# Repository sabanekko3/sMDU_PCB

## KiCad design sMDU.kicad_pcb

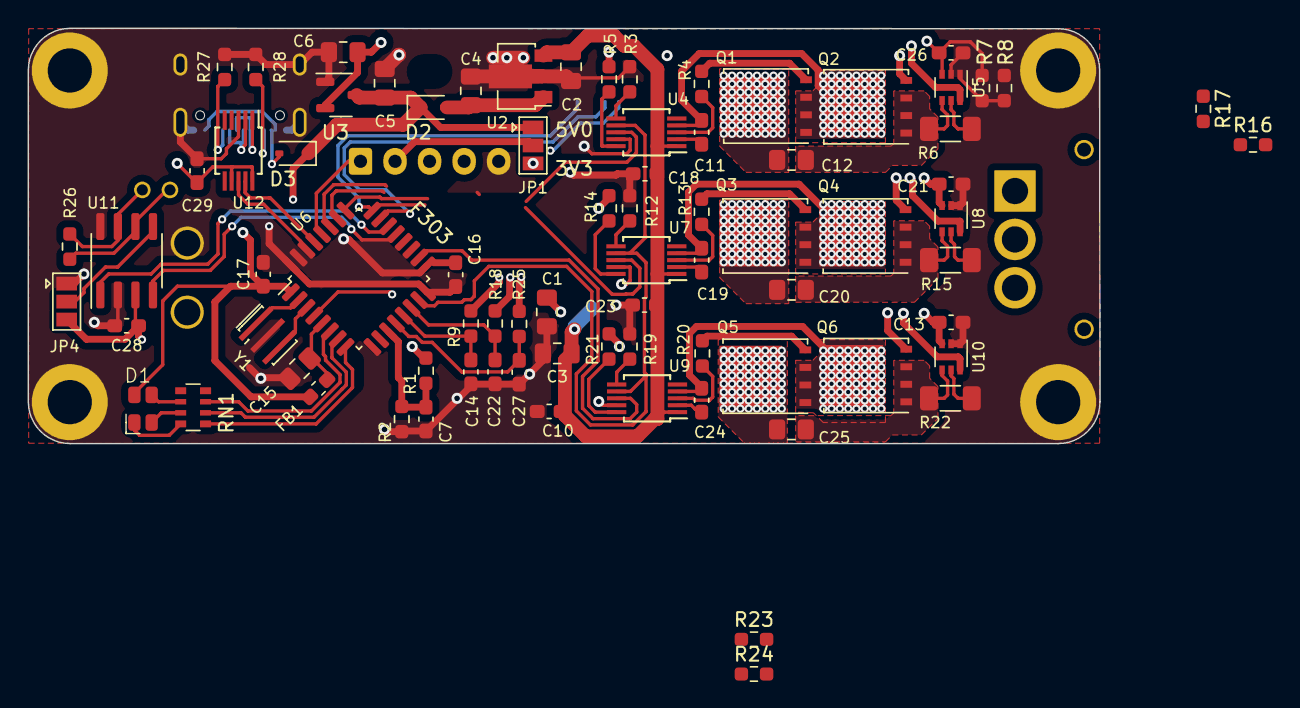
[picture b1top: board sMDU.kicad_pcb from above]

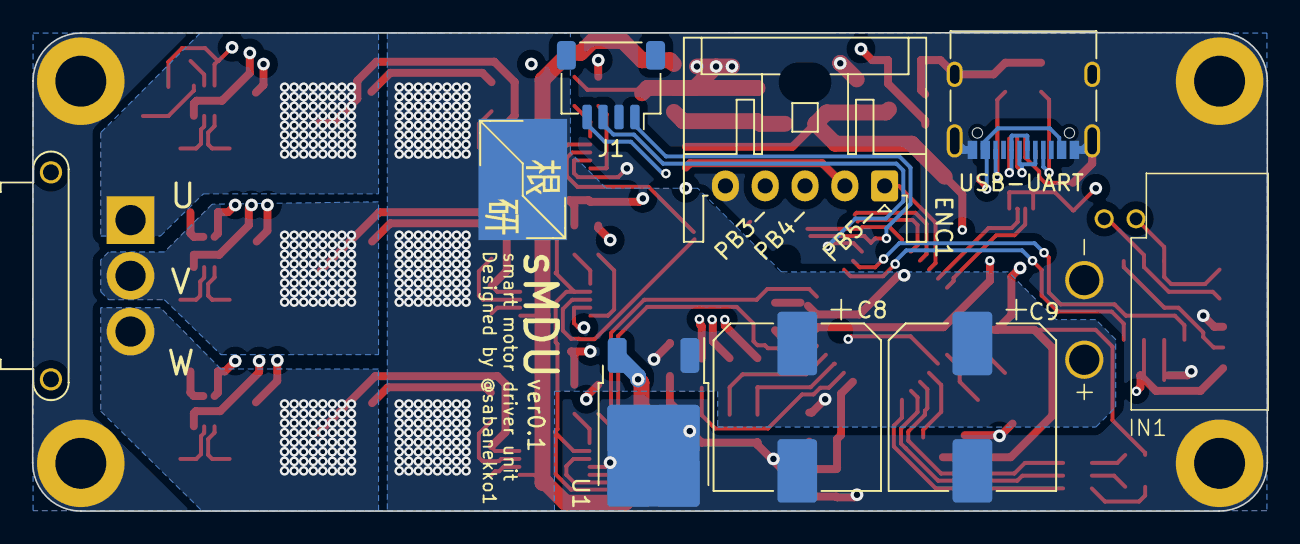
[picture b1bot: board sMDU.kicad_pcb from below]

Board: 4 copper layers, 77.6 x 30.1 mm, 91 parts (9 on the bottom side), 71 nets.

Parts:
C1, C2, C3, C4, C5, C6, C12, C15, C20, C25: 4.7u; C_0805_2012Metric_Pad1.18x1.45mm_HandSolder
C7, C13, C16, C17, C21, C26, C28, C29: 0.1u; C_0603_1608Metric_Pad1.08x0.95mm_HandSolder
C8, C9: 330u; CP_Elec_10x10
C10, C11, C18, C19, C23, C24: 1u; C_0603_1608Metric_Pad1.08x0.95mm_HandSolder
C14, C22, C27: 0.01u; C_0603_1608Metric_Pad1.08x0.95mm_HandSolder
D1: LED_BARG; SMD,1.8x2mm
D2, D3: D; D_SOD-323
ENC1: Conn_01x05; JST_XA_S05B-XASK-1_1x05_P2.50mm_Horizontal
FB1: FerriteBead; L_0603_1608Metric_Pad1.05x0.95mm_HandSolder
H1, H2, H3, H4: MountingHole_Pad; MountingHole_3.2mm_M3_ISO14580_Pad
IN1: XT30PW22
J1: Conn_01x04; JST_SH_SM04B-SRSS-TB_1x04-1MP_P1.00mm_Horizontal
J2: USB_C_Receptacle_USB2.0; USB_C_Receptacle_XKB_U262-16XN-4BVC11
JP1: C2P; SolderJumper-3_P1.3mm_Open_Pad1.0x1.5mm
JP4: Jumper_3_Open; SolderJumper-3_P1.3mm_Open_Pad1.0x1.5mm
OUT1: Conn_01x03; AMASS_MR30PW-FB_1x03_P3.50mm_Horizontal
Q1, Q2, Q3, Q4, Q5, Q6: SWHA088R06VT; TDSON-8-1
R1, R7, R8, R16, R17, R23, R24: 10k; R_0603_1608Metric_Pad0.98x0.95mm_HandSolder
R2: 1k; R_0603_1608Metric_Pad0.98x0.95mm_HandSolder
R3, R12, R19: 100k; R_0603_1608Metric_Pad0.98x0.95mm_HandSolder
R4, R5, R13, R14, R20, R21: 22; R_0603_1608Metric_Pad0.98x0.95mm_HandSolder
R6, R15, R22: 1m; R_1206_3216Metric_Pad1.30x1.75mm_HandSolder
R9, R18, R25: 100; R_0603_1608Metric_Pad0.98x0.95mm_HandSolder
R26: 120; R_0603_1608Metric_Pad0.98x0.95mm_HandSolder
R27, R28: 5.1k; R_0603_1608Metric_Pad0.98x0.95mm_HandSolder
RN1: 1k; R_Array_Convex_4x0603
TP1: LOGO; sabanegi
U1: 9V_LR; TO-252-2
U2: L78L05_SOT89; SOT-89-3
U3: XC6206PxxxMR; SOT-23-3
U4, U7, U9: DGD0506A; MSOP-10_3x3mm_P0.5mm
U5, U8, U10: INA199x1DCK; SOT-363_SC-70-6
U6: STM32F303K8Tx; LQFP-32_7x7mm_P0.8mm
U11: MCP2551-I-SN; SOIC-8_3.9x4.9mm_P1.27mm
U12: CH340E; MSOP-10_3x3mm_P0.5mm
Y1: Resonator; Resonator_SMD_Murata_CSTxExxV-3Pin_3.0x1.1mm_HandSoldering

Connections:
+3.3V: C6.1, C13.1, C16.1, C17.1, C21.1, C26.1, C29.2, D1.2 (A), FB1.1, JP1.3 (B), R7.1, R16.1, R23.1, U3.2 (VO), U5.3 (V+), U6.1 (VDD), U6.17 (VDD), U8.3 (V+), U10.3 (V+), U12.7 (VCC), U12.10 (V3)
+5V: C5.1, C28.1, D2.1 (K), D3.1 (K), JP1.1 (A), JP4.3 (B), U3.3 (VI), U11.3 (VDD)
+9V: C2.1, C3.1, C10.2, C18.2, C23.2, U1.3 (OUT), U2.3 (IN), U4.1 (VCC), U7.1 (VCC), U9.1 (VCC)
+BATT: C1.1, C8.1, C9.1, C12.1, C20.1, C25.1, IN1.1 (+), Q1.5 (D), Q3.5 (D), Q5.5 (D), R1.1, TP1.1, U1.1 (IN)
/BRIDGE1/I: C22.1, R18.2, U6.14 (PB0)
/BRIDGE1/OUT: C19.1, OUT1.2, Q3.1 (S), Q3.2 (S), Q3.3 (S), Q4.5 (D), U7.4 (VS)
/BRIDGE1/PWM: U6.19 (PA9), U7.8 (IN)
/BRIDGE2/I: C27.1, R25.2, U6.12 (PA6)
/BRIDGE2/OUT: C24.1, OUT1.3, Q5.1 (S), Q5.2 (S), Q5.3 (S), Q6.5 (D), U9.4 (VS)
/BRIDGE2/PWM: U6.18 (PA8), U9.8 (IN)
/BRIDGE/EN: U4.7 (EN), U6.15 (PB1), U7.7 (EN), U9.7 (EN)
/BRIDGE/I: C14.1, R9.2, U6.13 (PA7)
/BRIDGE/OUT: C11.1, OUT1.1, Q1.1 (S), Q1.2 (S), Q1.3 (S), Q2.5 (D), U4.4 (VS)
/BRIDGE/PWM: U4.8 (IN), U6.20 (PA10)
/CAN/CAN-H: IN1.3 (S1), R26.1, U11.7 (CANH)
/CAN/CAN-L: IN1.4 (S2), R26.2, U11.6 (CANL)
/CAN/CAN_RX: U6.21 (PA11), U11.4 (RXD)
/CAN/CAN_TX: U6.22 (PA12), U11.1 (TXD)
/MCU/I2C_SCL: ENC1.4, U6.25 (PA15), U6.26 (PB3)
/MCU/LED_B: RN1.3 (R3.1), U6.6 (PA0)
/MCU/LED_G: RN1.2 (R2.1), U6.7 (PA1)
/MCU/LED_R: RN1.1 (R1.1), U6.8 (PA2)
/MCU/NRST: J1.4, U6.4 (NRST)
/MCU/PB5: ENC1.1, U6.9 (PA3), U6.28 (PB5)
/MCU/POWER_V: C7.1, R1.2, R2.1, U6.11 (PA5)
/MCU/SWCLK: ENC1.3, J1.1, U6.10 (PA4), U6.24 (PA14), U6.27 (PB4)
/MCU/SWDIO: J1.3, U6.23 (PA13)
/MCU/UART_RX: U6.30 (PB7), U12.8 (TXD)
/MCU/UART_TX: U6.29 (PB6), U12.9 (RXD)
GND: C1.2, C2.2, C3.2, C4.2, C5.2, C6.2, C7.2, C8.2, C9.2, C10.1, C13.2, C14.2, C15.2, C16.2, C17.2, C18.1, C21.2, C22.2, C23.1, C26.2, C27.2, C28.2, C29.1, ENC1.5, H1.1, H2.1, H3.1, H4.1, IN1.2 (-), J1.2, J2.A1 (GND), J2.A12 (GND), J2.B1 (GND), J2.B12 (GND), J2.S1 (SHIELD), JP4.1 (A), R2.2, R3.2, R6.2, R8.2, R12.2, R15.2, R17.2, R19.2, R22.2, R24.2, R27.2, R28.2, U1.2 (GND), U2.2 (GND), U3.1 (GND), U4.9 (COM), U5.2 (GND), U5.5 (-), U6.16 (VSS), U6.31 (BOOT0), U6.32 (VSS), U7.9 (COM), U8.2 (GND), U8.5 (-), U9.9 (COM), U10.2 (GND), U10.5 (-), U11.2 (VSS), U11.8 (Rs), U12.3 (GND), Y1.2
unnamed: D1.1 (BK), RN1.8 (R1.2)
unnamed: D1.4 (GK), RN1.7 (R2.2)
unnamed: D1.3 (RK), RN1.6 (R3.2)
unnamed: C4.1, D2.2 (A), U2.1 (OUT)
unnamed: D3.2 (A), J2.A4 (VBUS), J2.A9 (VBUS), J2.B4 (VBUS), J2.B9 (VBUS)
unnamed: ENC1.2, JP1.2 (C)
unnamed: J2.A5 (CC1), R27.1
unnamed: J2.B5 (CC2), R28.1
unnamed: JP4.2 (C), U11.5 (Vref)
unnamed: Q1.4 (G), R4.2
unnamed: Q2.4 (G), R5.2
unnamed: Q3.4 (G), R13.2
unnamed: Q4.4 (G), R14.2
unnamed: Q5.4 (G), R20.2
unnamed: Q6.4 (G), R21.2
unnamed: R9.1, U5.6
unnamed: R18.1, U8.6
unnamed: R25.1, U10.6
unnamed: R3.1, U4.6 (DT)
unnamed: R4.1, U4.3 (HO)
unnamed: R5.1, U4.10 (LO)
unnamed: C11.2, U4.2 (Vboot)
unnamed: C12.2, Q2.1 (S), Q2.2 (S), Q2.3 (S), R6.1, U5.4 (+)
unnamed: R7.2, R8.1, U5.1 (REF)
unnamed: U6.2 (PF0), Y1.1
unnamed: U6.3 (PF1), Y1.3
unnamed: C15.1, FB1.2, U6.5 (VDDA)
unnamed: R12.1, U7.6 (DT)
unnamed: R13.1, U7.3 (HO)
unnamed: R14.1, U7.10 (LO)
unnamed: C19.2, U7.2 (Vboot)
unnamed: C20.2, Q4.1 (S), Q4.2 (S), Q4.3 (S), R15.1, U8.4 (+)
unnamed: R16.2, R17.1, U8.1 (REF)
unnamed: R19.1, U9.6 (DT)
unnamed: R20.1, U9.3 (HO)
unnamed: R21.1, U9.10 (LO)
unnamed: C24.2, U9.2 (Vboot)
unnamed: C25.2, Q6.1 (S), Q6.2 (S), Q6.3 (S), R22.1, U10.4 (+)
unnamed: R23.2, R24.1, U10.1 (REF)
unnamed: J2.A6 (D+), J2.B6 (D+), U12.1 (UD+)
unnamed: J2.A7 (D-), J2.B7 (D-), U12.2 (UD-)

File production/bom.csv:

Designator,Footprint,Quantity,Value,LCSC Part #
C1,0805,1,4.7u,C1779
C10,0603,1,1u,C15849
C11,0603,1,1u,C15849
C12,0805,1,4.7u,C1779
C13,0603,1,0.1u,C14663
C14,0603,1,0.01u,C57112
C15,0805,1,4.7u,C1779
C16,0603,1,0.1u,C14663
C17,0603,1,0.1u,C14663
C18,0603,1,1u,C15849
C19,0603,1,1u,C15849
C2,0805,1,4.7u,C1779
C20,0805,1,4.7u,C1779
C21,0603,1,0.1u,C14663
C22,0603,1,0.01u,C57112
C23,0603,1,1u,C15849
C24,0603,1,1u,C15849
C25,0805,1,4.7u,C1779
C26,0603,1,0.1u,C14663
C27,0603,1,0.01u,C57112
C28,0603,1,0.1u,C14663
C29,0603,1,0.1u,C14663
C3,0805,1,4.7u,C1779
C4,0805,1,4.7u,C1779
C5,0805,1,4.7u,C1779
C6,0805,1,4.7u,C1779
C7,0603,1,0.1u,C15849
"C8, C9",CP_Elec_10x10,2,330u,
D1,"SMD,1.8x2mm",1,LED_BARG,C513367
"D2, D3",D_SOD-323,2,D,C191023
ENC1,JST_XA_S05B-XASK-1_1x05_P2.50mm_Horizontal,1,Conn_01x05,
FB1,0603,1,FerriteBead,C1002
"H1, H2, H3, H4",MountingHole_3.2mm_M3_ISO14580_Pad,4,MountingHole_Pad,
IN1,XT30PW22,1,~,
J1,JST_SH_SM04B-SRSS-TB_1x04-1MP_P1.00mm_Horizontal,1,Conn_01x04,
J2,USB_C_Receptacle_XKB_U262-16XN-4BVC11,1,USB_C_Receptacle_USB2.0,
"JP1, JP2",SolderJumper-3_P1.3mm_Open_Pad1.0x1.5mm,2,Jumper_3_Open,
OUT1,AMASS_MR30PW-FB_1x03_P3.50mm_Horizontal,1,Conn_01x03,
"Q1, Q2, Q3, Q4, Q5, Q6",TDSON-8-1,6,BSC050N04LS,C5151871
R1,0603,1,10k,C25804
R10,0603,1,22,C23345
R11,1206,1,1m,C914835
R12,0603,1,100,C22775
R13,0603,1,100k,C25803
R14,0603,1,22,C23345
R15,0603,1,22,C23345
R16,1206,1,1m,C914835
R17,0603,1,100,C22775
R18,0603,1,120,
R19,0603,1,5.1k,C23186
R2,0603,1,1k,C21190
R20,0603,1,5.1k,C23186
R3,0603,1,100k,C25803
R4,0603,1,22,C23345
R5,0603,1,22,C23345
R6,1206,1,1m,C914835
R7,0603,1,100,C22775
R8,0603,1,100k,C25803
R9,0603,1,22,C23345
RN1,R_Array_Convex_4x0603,1,1k,C25510
TP1,sabanegi,1,LOGO,
U1,TO-252-2,1,9V_LR,
"U10, U5, U8",SOT-363_SC-70-6,3,INA199xxDCK,C2857879
U11,SOIC-8_3.9x4.9mm_P1.27mm,1,MCP2551-I-SN,
U12,MSOP-10_3x3mm_P0.5mm,1,CH340E,C99652
U13,SOT-23-3,1,XC6206PxxxMR,C5446
U2,SOT-89-3,1,L78L05_SOT89,C16106
"U4, U7, U9",MSOP-10_3x3mm_P0.5mm,3,DGD0506A,C460681
U6,LQFP-32_7x7mm_P0.8mm,1,STM32F303K8Tx,
Y1,Resonator_SMD_Murata_CSTxExxV-3Pin_3.0x1.1mm_HandSoldering,1,Resonator,C1870467

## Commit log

2023-06-22 first
2023-06-22 export pdf
2023-07-16 なにか変えた
